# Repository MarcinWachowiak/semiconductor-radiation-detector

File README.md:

# Semiconductor Radiation Detector
<div align="justify">
Radiation detector based on PIN diode with extensive signal processing. The signal chain consists of multiple stages such as bootstrapped preamplifier, filtering, baseline restorer, sample and hold, and set of comparators detecting slopes of pulses. The signal processing board provides analog output for ADC along with digital signals triggering measurements. <a href="https://hackaday.io/project/159909-gamma-pin-semiconductor-radiation-detector">Hackaday project log</a>

</div>

  - **Manufactured prototypes**

  - **Preamplifier board**

  - **Signal processing board**

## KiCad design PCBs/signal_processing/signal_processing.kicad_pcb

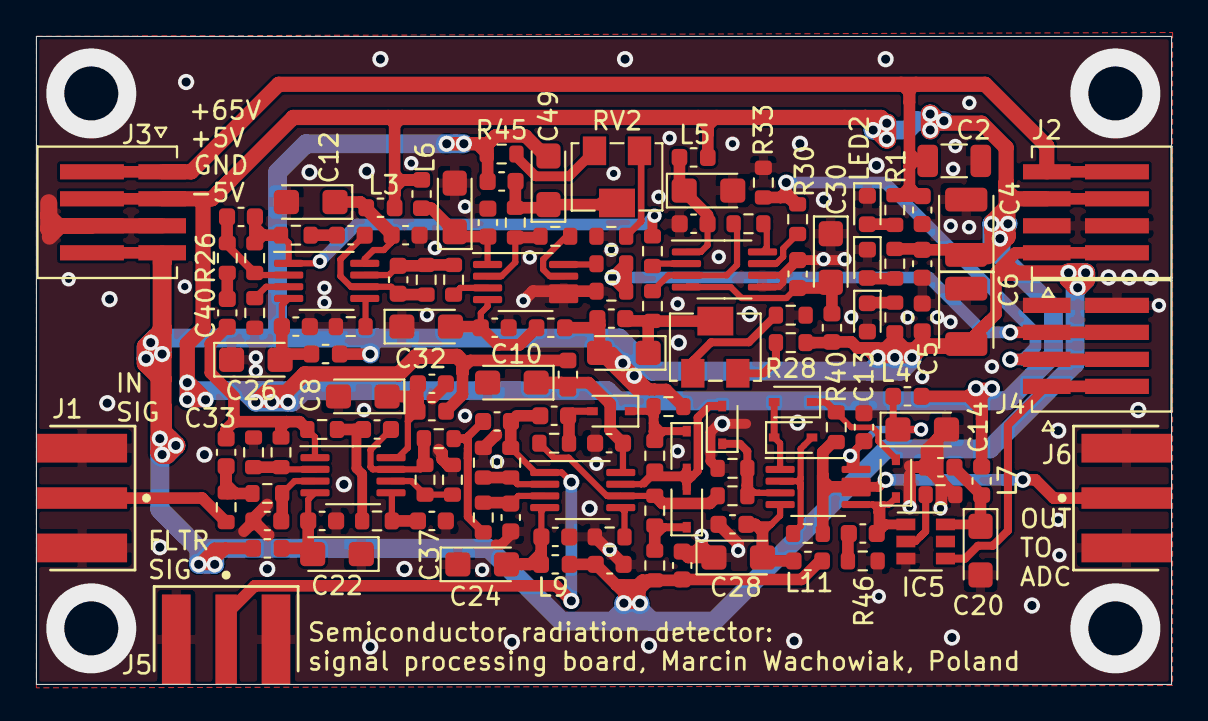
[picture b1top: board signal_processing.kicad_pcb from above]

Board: 2 copper layers, 63.1 x 36.0 mm, 135 parts (0 on the bottom side), 72 nets.

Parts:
C1: 1n/100V; C_0603_1608Metric
C2: 4,7u/50V; C_1206_3216Metric
C3, C5, C7, C9, C11, C13, C15, C17, C19, C21, C23, C25, C27, C29, C31, C40, C41, C43, C44, C48: 100n/50V; C_0603_1608Metric
C4, C6: 47u/6V; CP_EIA-3528-21_Kemet-B
C8, C10, C12, C14, C16, C18, C20, C22, C24, C26, C28, C30, C32, C42, C49: 4,7u/6V; CP_EIA-3216-18_Kemet-A
C33, C34, C35, C36, C37: 2,2n/50V; C_0603_1608Metric
C38: 220p/50V; C_0603_1608Metric
C39: 10n/50V; C_0603_1608Metric
C45, C50: 1p/50V; C_0603_1608Metric
C46: 470p/50V; C_0603_1608Metric
C47: 1n/50V; C_0603_1608Metric
D1, D2, D3, D4, D5, D6, D7: BAS140; D_SOD-323
IC1, IC2, IC3, IC4: AD8066; MSOP-8_3x3mm_P0.65mm
IC5: ADG701; SOT-23-6
IC6, IC7: LT1713; MSOP-8_3x3mm_P0.65mm
J1, J5, J6: CON-SMA-EDGE-S
J2, J3, J4: 874380443; 87438-0443
L1, L2, L3, L4, L5, L6, L7, L8, L9, L10, L11, L12, L13: 1u; L_0603_1608Metric
LED1, LED2, LED3: GREEN; LED_0603_1608Metric
R1: 43k; R_0603_1608Metric
R2, R3: 300; R_0603_1608Metric
R4: 390; R_0603_1608Metric
R5: 2,4k; R_0603_1608Metric
R6: 330; R_0603_1608Metric
R7, R39: 3,3k; R_0603_1608Metric
R8: 560; R_0603_1608Metric
R9: 18k; R_0603_1608Metric
R10: 820; R_0603_1608Metric
R11, R17, R18, R21, R26, R30, R41, R42: 1k; R_0603_1608Metric
R12: 680; R_0603_1608Metric
R13, R14: 270; R_0603_1608Metric
R15: 470; R_0603_1608Metric
R16, R45: 2,2k; R_0603_1608Metric
R19, R20, R27, R31: 1,6k; R_0603_1608Metric
R22, R29, R32, R36, R37, R38, R40, R47: 100; R_0603_1608Metric
R23: 10k; R_0603_1608Metric
R24: 520; R_0603_1608Metric
R25: 100k; R_0603_1608Metric
R28, R35: 1; R_0603_1608Metric
R33, R44: 2k; R_0603_1608Metric
R34: 470k; R_0603_1608Metric
R43: 22k; R_0603_1608Metric
R46: 22; R_0603_1608Metric
RV1: 10; Potentiometer_Bourns_3224W_Vertical
RV2: 500; Potentiometer_Bourns_3224W_Vertical

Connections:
+5V: C3.2, C4.1, J2.3_1, J2.3_2, J3.2_1, J3.2_2, L1.1, L2.1, L3.1, L4.1, L5.1, L6.1, L7.1, R2.1
-5V: C5.1, C6.2, C41.2, C42.2, C43.1, C44.1, C48.2, C49.2, J2.1_1, J2.1_2, J3.4_1, J3.4_2, L8.2, L9.2, L10.2, L11.2, L12.2, L13.2, R3.2, R27.1, R28.1, R31.1, R45.1
/+65V: C1.2, C2.1, J2.4_1, J2.4_2, J3.1_1, J3.1_2, R1.1
/ADC: IC4.6, IC4.7, J6.1, R36.1, R40.1
/BLR_OUT: D1.1, IC4.3, R16.2, R20.2
/FAST_FILTERED_SIG: C33.1, C40.2, IC1.1, R6.2, R10.1
/FILTERED_SIGNAL: C35.1, C39.2, IC2.1, J5.1, R12.1
/PULSE_DURATION: J4.2_1, J4.2_2, R30.2, R33.1
/RESET: IC5.4, J4.1_1, J4.1_2
/RISING_SLOPE: J4.3_1, J4.3_2, R41.2, R44.1
/SIGNAL_INPUT: J1.1, R4.2
GND: C1.1, C2.2, C3.1, C4.2, C5.2, C6.1, C7.1, C8.2, C9.1, C10.2, C11.1, C12.2, C13.1, C14.2, C15.1, C16.2, C17.1, C18.2, C19.1, C20.2, C21.2, C22.1, C23.2, C24.1, C25.2, C26.1, C27.2, C28.1, C29.2, C30.1, C31.2, C32.1, C36.1, C37.1, C38.1, C43.2, C44.2, IC5.3, IC6.5, IC6.6, IC7.5, IC7.6, J1.2, J2.2_1, J2.2_2, J3.3_1, J3.3_2, J4.4_1, J4.4_2, J5.2, J6.2, LED1.2, LED2.1, LED3.1, R13.2, R14.2, R15.2, R18.2, R20.1, R22.2, R32.2, R33.2, R38.2, R39.2, R44.2, R46.2, R47.2
unnamed: C7.2, C8.1, IC1.8, L1.2
unnamed: C9.2, C10.1, IC2.8, L2.2
unnamed: C11.2, C12.1, IC3.8, L3.2
unnamed: C13.2, C14.1, IC4.8, L4.2
unnamed: C15.2, C16.1, IC6.1, L5.2
unnamed: C17.2, C18.1, IC7.1, L6.2
unnamed: C19.2, C20.1, IC5.6, L7.2
unnamed: C21.1, C22.2, IC1.4, L8.1
unnamed: C23.1, C24.2, IC2.4, L9.1
unnamed: C25.1, C26.2, IC3.4, L10.1
unnamed: C27.1, C28.2, IC4.4, L11.1
unnamed: C29.1, C30.2, IC6.4, L12.1
unnamed: C31.1, C32.2, IC7.4, L13.1
unnamed: C33.2, R4.1, R5.2
unnamed: C34.1, IC1.7, R8.2, R11.1
unnamed: C34.2, R6.1, R7.2
unnamed: C35.2, R8.1, R9.2
unnamed: C36.2, IC1.3, R5.1
unnamed: C37.2, IC1.5, R7.1
unnamed: C38.2, IC2.3, R9.1
unnamed: C39.1, D4.2, R17.2
unnamed: C40.1, R26.1
unnamed: C41.1, C42.1, R24.2, RV1.2
unnamed: C45.1, IC3.7, R34.1, R37.2
unnamed: C45.2, C46.1, IC3.6, R34.2
unnamed: C46.2, R35.1
unnamed: C47.1, D7.1, IC4.5, IC5.1
unnamed: C47.2, R46.1
unnamed: C48.1, C49.1, R42.2, RV2.2
unnamed: C50.1, IC3.1, R21.1, R29.2, R35.2
unnamed: C50.2, IC3.2, R21.2, R26.2
unnamed: D1.2, D2.2, D3.2, IC2.7, R19.2
unnamed: D2.1, R23.2, R27.2
unnamed: D3.1, D4.1, R19.1, R31.2
unnamed: D5.1, D6.2, IC4.1
unnamed: D5.2, IC4.2, R36.2
unnamed: D6.1, D7.2, R40.2
unnamed: IC1.2, R10.2, R13.1
unnamed: IC1.6, R11.2, R14.1
unnamed: IC2.2, R12.2, R15.1
unnamed: IC2.5, R22.1
unnamed: IC2.6, R16.1, R17.1, R23.1
unnamed: IC3.3, R32.1
unnamed: IC3.5, R38.1
unnamed: IC5.2, R47.1
unnamed: IC6.2, R29.1
unnamed: IC6.3, R24.1, R25.2
unnamed: IC6.7, R30.1
unnamed: IC6.8, R25.1
unnamed: IC7.2, R42.1, R43.2
unnamed: IC7.3, R37.1
unnamed: IC7.7, R43.1
unnamed: IC7.8, R41.1
unnamed: LED1.1, R3.1
unnamed: LED2.2, R1.2
unnamed: LED3.2, R2.2
unnamed: R18.1, RV1.1
unnamed: R28.2, RV1.3
unnamed: R39.1, RV2.1
unnamed: R45.2, RV2.3

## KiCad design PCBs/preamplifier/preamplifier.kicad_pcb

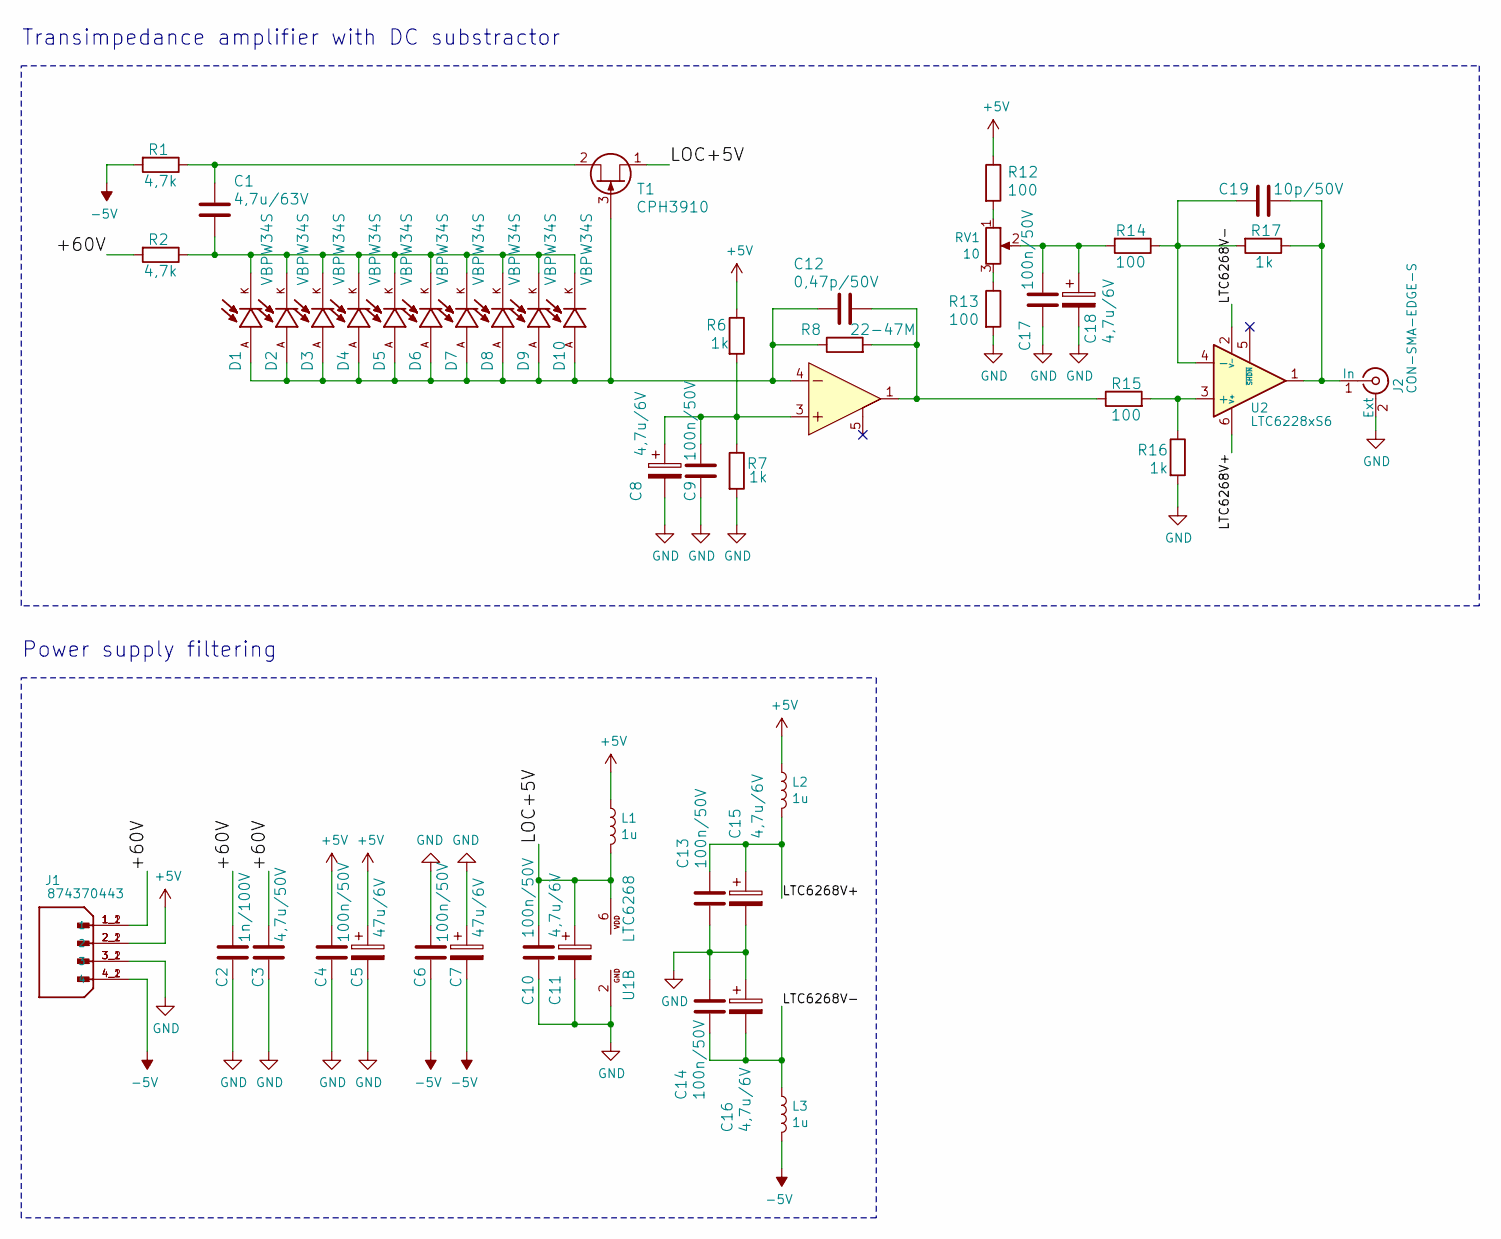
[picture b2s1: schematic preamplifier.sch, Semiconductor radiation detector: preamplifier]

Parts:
C1: 4,7u/63V; C_1206_3216Metric
C2: 1n/100V; C_0603_1608Metric
C3: 4,7u/50V; C_1206_3216Metric
C4, C6, C9, C10, C13, C14, C17: 100n/50V; C_0603_1608Metric
C5, C7: 47u/6V; CP_EIA-3528-21_Kemet-B
C8, C11, C15, C16, C18: 4,7u/6V; CP_EIA-3216-18_Kemet-A
C12: 0,47p/50V; C_0603_1608Metric
C19: 10p/50V; C_0603_1608Metric
D1, D2, D3, D4, D5, D6, D7, D8, D9, D10: VBPW34S; XDCR_VBPW34S; PARTREV 1.2
J1: 874370443; 87437-0443; PARTREV A
J2: CON-SMA-EDGE-S; digikey description CONN SMA JACK STR EDGE MNT
L1, L2, L3: 1u; L_0603_1608Metric
R1, R2: 4,7k; R_0603_1608Metric
R6, R7, R16, R17: 1k; R_0603_1608Metric
R8: 22-47M; R_0603_1608Metric
R12, R13, R14, R15: 100; R_0603_1608Metric
RV1: 10; Potentiometer_Bourns_3224W_Vertical
T1: CPH3910; SOT-23
U1: LTC6268; TSOT-23-6
U2: LTC6228xS6; TSOT-23-6

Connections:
+5V: C4.2, C5.1, J1.2_1 (2), J1.2_2 (2), L1.1, L2.1, R6.1, R12.1
-5V: C6.1, C7.2, J1.4_1 (4), J1.4_2 (4), L3.2, R1.2
/+60V: C2.2, C3.1, J1.1_1 (1), J1.1_2 (1), R2.2
/LOC+5V: C10.2, C11.1, L1.2, T1.1 (S), U1.6 (VDD)
/LTC6268V+: C13.2, C15.1, L2.2, U2.6 (V+)
/LTC6268V-: C14.1, C16.2, L3.1, U2.2 (V-)
GND: C2.1, C3.2, C4.1, C5.2, C6.2, C7.1, C8.2, C9.1, C10.1, C11.2, C13.1, C14.2, C15.2, C16.1, C17.2, C18.2, J1.3_1 (3), J1.3_2 (3), J2.2 (Ext), R7.2, R13.2, R16.2, U1.2 (GND)
unnamed: C1.1, D1.K, D2.K, D3.K, D4.K, D5.K, D6.K, D7.K, D8.K, D9.K, D10.K, R2.1
unnamed: C1.2, R1.1, T1.2 (D)
unnamed: C8.1, C9.2, R6.2, R7.1, U1.3 (+IN)
unnamed: C12.1, R8.2, R15.1, U1.1 (OUT)
unnamed: C12.2, D1.A, D2.A, D3.A, D4.A, D5.A, D6.A, D7.A, D8.A, D9.A, D10.A, R8.1, T1.3 (G), U1.4 (-IN)
unnamed: C17.1, C18.1, R14.2, RV1.2
unnamed: C19.1, R14.1, R17.2, U2.4 (-)
unnamed: C19.2, J2.1 (In), R17.1, U2.1
unnamed: R12.2, RV1.1
unnamed: R13.1, RV1.3
unnamed: R15.2, R16.1, U2.3 (+)

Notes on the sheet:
Transimpedance amplifier with DC substractor
Power supply filtering

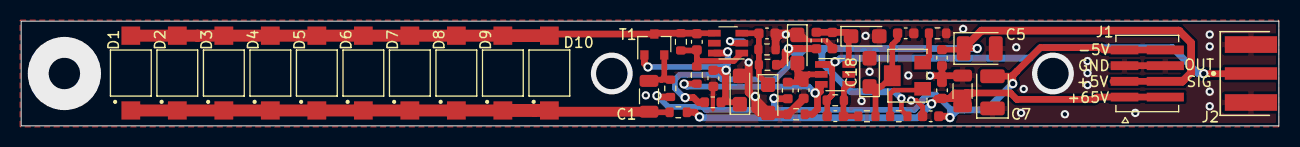
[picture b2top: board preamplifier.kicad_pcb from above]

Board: 2 copper layers, 120.2 x 10.0 mm, 49 parts (0 on the bottom side), 18 nets.

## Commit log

2021-09-29 Reorganization of pcb files
2021-09-30 finished preamplifier board redesigning
2021-09-30 sp board update
2021-10-01 Init STM32 experimental code
2021-10-01 finished pcbs
2021-10-01 reapply gitignore
2021-10-30 check photos
2022-02-19 Updated code and solved CDC transmit issue
2022-10-29 Update license
